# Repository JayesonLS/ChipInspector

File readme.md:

Circuits for Arbitrary Inspection/Operation of Integrated Circuits
==================================================================

ChipInspector24
---------------

Circuit that made use of the many 5v pins on a Teensy++. Never 
tested as the need came about for a 50 pin device.

ChipInspector40
---------------

Circuit using an inexpensive Arduino Pro Micro and many input
and output shift registers. Very incomplete.

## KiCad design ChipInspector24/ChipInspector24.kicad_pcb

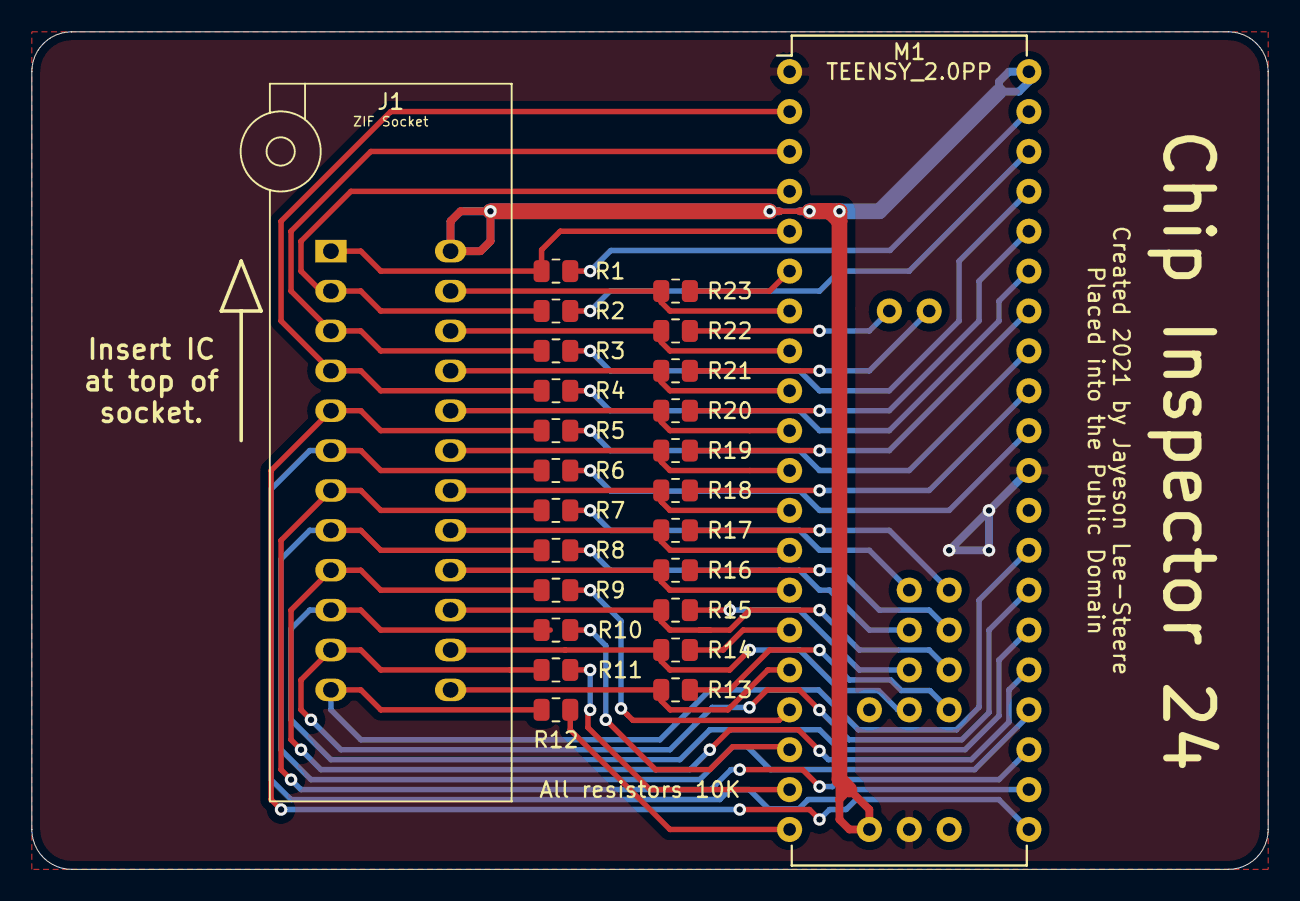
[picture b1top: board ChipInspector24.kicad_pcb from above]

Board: 2 copper layers, 78.7 x 53.3 mm, 25 parts (0 on the bottom side), 48 nets.

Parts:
J1: ZIF Socket; DIP_Socket-24_W4.3_W5.08_W7.62_W10.16_W10.9_3M_224-5248-00-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
M1: TEENSY_2.0PP; Teensy_2.0PP
R1, R2, R3, R4, R5, R6, R7, R8, R9, R10, R11, R12, R13, R14, R15, R16, R17, R18, R19, R20, R21, R22, R23: 10K; R_0805_2012Metric

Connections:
GND: M1.1, M1.30, M1.42
P01: J1.1, M1.5, R1.1
P01R: M1.39, R1.2
P02: J1.2, M1.4, R2.1
P02R: M1.38, R2.2
P03: J1.3, M1.3, R3.1
P03R: M1.37, R3.2
P04: J1.4, M1.2, R4.1
P04R: M1.35, R4.2
P05: J1.5, M1.21, R5.1
P05R: M1.33, R5.2
P06: J1.6, M1.22, R6.1
P06R: M1.31, R6.2
P07: J1.7, M1.23, R7.1
P07R: M1.45, R7.2
P08: J1.8, M1.24, R8.1
P08R: M1.46, R8.2
P09: J1.9, M1.25, R9.1
P09R: M1.17, R9.2
P10: J1.10, M1.26, R10.1
P10R: M1.18, R10.2
P11: J1.11, M1.27, R11.1
P11R: M1.19, R11.2
P12: J1.12, M1.28, R12.1
P12R: M1.20, R12.2
P13: J1.13, M1.16, R13.1
P13R: M1.49, R13.2
P14: J1.14, M1.48, R14.1
P14R: M1.15, R14.2
P15: J1.15, M1.50, R15.1
P15R: M1.47, R15.2
P16: J1.16, M1.14, R16.1
P16R: M1.51, R16.2
P17: J1.17, M1.13, R17.1
P17R: M1.52, R17.2
P18: J1.18, M1.12, R18.1
P18R: M1.32, R18.2
P19: J1.19, M1.11, R19.1
P19R: M1.34, R19.2
P20: J1.20, M1.10, R20.1
P20R: M1.36, R20.2
P21: J1.21, M1.9, R21.1
P21R: M1.53, R21.2
P22: J1.22, M1.8, R22.1
P22R: M1.54, R22.2
P23: J1.23, M1.7, R23.1
P23R: M1.6, R23.2
VCC: J1.24, M1.40, M1.41

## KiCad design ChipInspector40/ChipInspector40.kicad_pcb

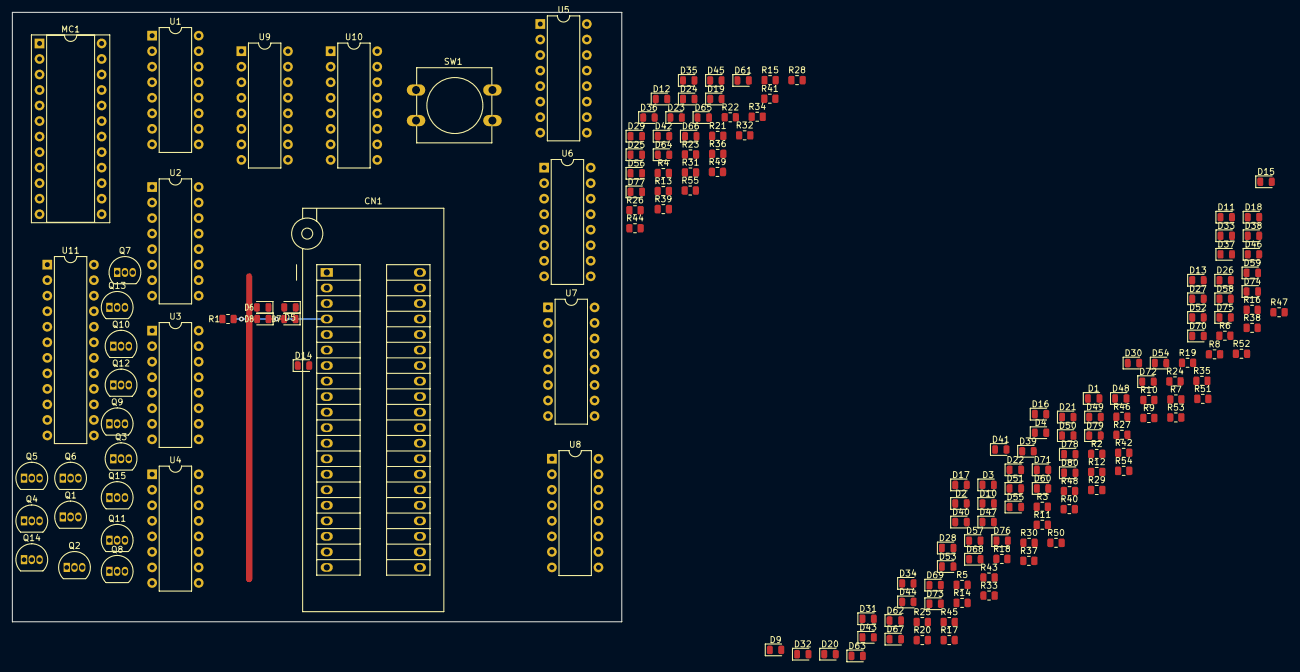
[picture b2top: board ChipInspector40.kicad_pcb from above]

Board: 2 copper layers, 99.7 x 99.7 mm, 164 parts (0 on the bottom side), 120 nets.

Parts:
CN1: 40 Pin ZIF; 3M_Textool_240-1288-00-0602J_2x20_P2.54mm
D1, D2, D3, D4, D5, D6, D7, D8, D9, D10, D11, D12, D13, D14, D15, D16, D17, D18, D19, D20, D21, D22, D23, D24, D25, D26, D27, D28, D29, D30, D31, D32, D33, D34, D35, D36, D37, D38, D39, D40, D41, D42, D43, D44, D45, D46, D47, D48, D49, D50, D51, D52, D53, D54, D55, D56, D57, D58, D59, D60, D61, D62, D63, D64, D65, D66, D67, D68, D69, D70, D71, D72, D73, D74, D75, D76, D77, D78, D79, D80: 1N4148; D_0805_2012Metric
MC1: ARDUINO_PRO_MICRO; DIP-24_W10.16mm_Socket
Q1, Q2, Q3, Q4, Q5, Q6, Q7, Q8, Q9, Q10, Q11, Q12, Q13, Q14, Q15: PN2222A; TO-92_Inline
R1, R2, R3, R4, R5, R6, R7, R8, R9, R10, R11, R12, R13, R14, R15, R16, R17, R18, R19, R20, R21, R22, R23, R24, R25, R26, R27, R28, R29, R30, R31, R32, R33, R34, R35, R36, R37, R38, R39, R40: 10K; R_0805_2012Metric
R41, R42, R43, R44, R45, R46, R47, R48, R49, R50, R51, R52, R53, R54, R55: 1K; R_0805_2012Metric
SW1: Reset; SW_PUSH-12mm
U1, U2, U3, U4, U5: 74LS/HC165; DIP-16_W7.62mm
U6, U7, U8, U9, U10: 74LS/HC595; DIP-16_W7.62mm
U11: 74LS154; DIP-24_W7.62mm

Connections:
/PIN1: CN1.1, D1.2, D2.1, R1.2, U1.11
/PIN1_DRIVE: R1.1, U6.15
/PIN2: CN1.2, D3.2, D4.1, R2.2, U1.12
/PIN2_DRIVE: R2.1, U6.1
/PIN2_READ: Q1.3, Q2.3
/PIN3: CN1.3, D5.2, D6.1, R3.2, U1.13
/PIN3_DRIVE: R3.1, U6.2
/PIN4: CN1.4, D7.2, D8.1, R4.2, U1.14
/PIN4_DRIVE: R4.1, U6.3
/PIN5: CN1.5, D9.2, D10.1, R5.2, U1.3
/PIN5_DRIVE: R5.1, U6.4
/PIN6: CN1.6, D11.2, D12.1, R6.2, U1.4
/PIN6_DRIVE: R6.1, U6.5
/PIN7: CN1.7, D13.2, D14.1, R7.2, U1.5
/PIN7_DRIVE: R7.1, U6.6
/PIN8: CN1.8, D15.2, D16.1, R8.2, U1.6
/PIN8_DRIVE: R8.1, U6.7
/PIN9: CN1.9, D17.2, D18.1, R9.2, U2.11
/PIN9_DRIVE: R9.1, U7.15
/PIN10: CN1.10, D19.2, D20.1, R10.2, U2.12
/PIN10_DRIVE: R10.1, U7.1
/PIN11: CN1.11, D21.2, D22.1, R11.2, U2.13
/PIN11_DRIVE: R11.1, U7.2
/PIN12: CN1.12, D23.2, D24.1, R12.2, U2.14
/PIN12_DRIVE: R12.1, U7.3
/PIN13: CN1.13, D25.2, D26.1, R13.2, U2.3
/PIN13_DRIVE: R13.1, U7.4
/PIN14: CN1.14, D27.2, D28.1, R14.2, U2.4
/PIN14_DRIVE: R14.1, U7.5
/PIN15: CN1.15, D29.2, D30.1, R15.2, U2.5
/PIN15_DRIVE: R15.1, U7.6
/PIN16: CN1.16, D31.2, D32.1, R16.2, U2.6
/PIN16_DRIVE: R16.1, U7.7
/PIN17: CN1.17, D33.2, D34.1, R17.2, U3.11
/PIN17_DRIVE: R17.1, U8.15
/PIN18: CN1.18, D35.2, D36.1, R18.2, U3.12
/PIN18_DRIVE: R18.1, U8.1
/PIN19: CN1.19, D37.2, D38.1, R19.2, U3.13
/PIN19_DRIVE: R19.1, U8.2
/PIN20: CN1.20, D39.2, D40.1, R20.2, U3.14
/PIN20_DRIVE: R20.1, U8.3
/PIN21: CN1.21, D41.2, D42.1, R40.2, U3.3
/PIN21_DRIVE: R40.1, U8.4
/PIN22: CN1.22, D43.2, D44.1, R39.2, U3.4
/PIN22_DRIVE: R39.1, U8.5
/PIN23: CN1.23, D45.2, D46.1, R38.2, U3.5
/PIN23_DRIVE: R38.1, U8.6
/PIN24: CN1.24, D47.2, D48.1, R37.2, U3.6
/PIN24_DRIVE: R37.1, U8.7
/PIN25: CN1.25, D49.2, D50.1, R36.2, U4.11
/PIN25_DRIVE: R36.1, U9.15
/PIN26: CN1.26, D51.2, D52.1, R35.2, U4.12
/PIN26_DRIVE: R35.1, U9.1
/PIN27: CN1.27, D53.2, D54.1, R34.2, U4.13
/PIN27_DRIVE: R34.1, U9.2
/PIN28: CN1.28, D55.2, D56.1, R33.2, U4.14
/PIN28_DRIVE: R33.1, U9.3
/PIN29: CN1.29, D57.2, D58.1, R32.2, U4.3
/PIN29_DRIVE: R32.1, U9.4
/PIN30: CN1.30, D59.2, D60.1, R31.2, U4.4
/PIN30_DRIVE: R31.1, U9.5
/PIN31: CN1.31, D61.2, D62.1, R30.2, U4.5
/PIN31_DRIVE: R30.1, U9.6
/PIN32: CN1.32, D63.2, D64.1, R29.2, U4.6
/PIN32_DRIVE: R29.1, U9.7
/PIN33: CN1.33, D65.2, D66.1, R28.2, U5.11
/PIN33_DRIVE: R28.1, U10.15
/PIN34: CN1.34, D67.2, D68.1, R27.2, U5.12
/PIN34_DRIVE: R27.1, U10.1
/PIN35: CN1.35, D69.2, D70.1, R26.2, U5.13
/PIN35_DRIVE: R26.1, U10.2
/PIN36: CN1.36, D71.2, D72.1, R25.2, U5.14
/PIN36_DRIVE: R25.1, U10.3
/PIN37: CN1.37, D73.2, D74.1, R24.2, U5.3
/PIN37_DRIVE: R24.1, U10.4
/PIN38: CN1.38, D75.2, D76.1, R23.2, U5.4
/PIN38_DRIVE: R23.1, U10.5
/PIN39: CN1.39, D77.2, D78.1, R22.2, U5.5
/PIN39_DRIVE: R22.1, U10.6
/PIN40: CN1.40, D79.2, D80.1, R21.2, U5.6
/PIN40_DRIVE: R21.1, U10.7
GND: D2.2, D4.2, D6.2, D8.2, D10.2, D12.2, D14.2, D16.2, D18.2, D20.2, D22.2, D24.2, D26.2, D28.2, D30.2, D32.2, D34.2, D36.2, D38.2, D40.2, D42.2, D44.2, D46.2, D48.2, D50.2, D52.2, D54.2, D56.2, D58.2, D60.2, D62.2, D64.2, D66.2, D68.2, D70.2, D72.2, D74.2, D76.2, D78.2, D80.2, MC1.3, MC1.4, Q1.1, Q2.1, Q3.1, Q4.1, Q5.1, Q6.1, Q7.1, Q8.1, Q9.1, Q10.1, Q11.1, Q12.1, Q13.1, Q14.1, Q15.1, SW1.2, U1.8, U1.10, U1.15, U2.8, U2.15, U3.8, U3.15, U4.8, U4.15, U5.8, U5.15, U6.8, U7.8, U8.8, U9.8, U10.8, U11.12, U11.18, U11.19
unnamed: MC1.22, SW1.1
unnamed: Q1.2, R41.1
unnamed: Q2.2, R42.1
unnamed: Q3.2, R43.1
unnamed: Q4.2, R44.1
unnamed: Q5.2, R45.1
unnamed: Q6.2, R46.1
unnamed: Q7.2, R47.1
unnamed: Q8.2, R48.1
unnamed: Q9.2, R49.1
unnamed: Q10.2, R50.1
unnamed: Q11.2, R51.1
unnamed: Q12.2, R52.1
unnamed: Q13.2, R53.1
unnamed: Q14.2, R54.1
unnamed: Q15.2, R55.1
unnamed: R41.2, U11.2
unnamed: R42.2, U11.3
unnamed: R43.2, U11.4
unnamed: R44.2, U11.5
unnamed: R45.2, U11.6
unnamed: R46.2, U11.7
unnamed: R47.2, U11.8
unnamed: R48.2, U11.9
unnamed: R49.2, U11.10
unnamed: R50.2, U11.11
unnamed: R51.2, U11.13
unnamed: R52.2, U11.14
unnamed: R53.2, U11.15
unnamed: R54.2, U11.16
unnamed: R55.2, U11.17
unnamed: U1.1, U2.1, U3.1, U4.1, U5.1
unnamed: U1.2, U2.2, U3.2, U4.2, U5.2
unnamed: U1.9, U2.10
unnamed: U2.9, U3.10
unnamed: U3.9, U4.10
unnamed: U4.9, U5.10
VCC: D1.1, D3.1, D5.1, D7.1, D9.1, D11.1, D13.1, D15.1, D17.1, D19.1, D21.1, D23.1, D25.1, D27.1, D29.1, D31.1, D33.1, D35.1, D37.1, D39.1, D41.1, D43.1, D45.1, D47.1, D49.1, D51.1, D53.1, D55.1, D57.1, D59.1, D61.1, D63.1, D65.1, D67.1, D69.1, D71.1, D73.1, D75.1, D77.1, D79.1, MC1.21, U1.16, U2.16, U3.16, U4.16, U5.16, U6.16, U7.16, U8.16, U9.16, U10.16, U11.24

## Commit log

2021-02-16 Add ChipInspector24.
2021-02-16 Add ChipInspector40.
2021-02-16 Add readme.
2021-02-16 Remove -bak files.
2021-02-27 Commit latest PCB edits and gerber export.
2021-05-05 Initial work on firmware for ChipInspector24.
2021-05-05 Add socket pin mappings for CI24 Firmware.
2022-06-04 Clarify licensing as it was unspecified.

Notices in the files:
ChipInspector24/ChipInspector24.kicad_pcb:
Placed into the Public Domain
